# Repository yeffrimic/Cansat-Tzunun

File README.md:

# 🌎 Estación de Calidad del Aire – Proyecto CanSat Tzunun

Este repositorio contiene el código, documentación, archivos de diseño y recursos educativos para implementar una **estación de monitoreo ambiental**, así como su versión miniaturizada adaptada al formato **CanSat**. El proyecto fue desarrollado por estudiantes de la **Universidad Mesoamericana, sede Quetzaltenango**, como una herramienta de medición ambiental portátil, educativa y de bajo costo.

---

## 🚀 Guía de Instalación – Heltec WiFi LoRa 32 (V3) en Arduino IDE

### Paso 1: Instalar el Arduino IDE
Descarga e instala la versión más reciente desde: [https://www.arduino.cc/en/software](https://www.arduino.cc/en/software)

### Paso 2: Añadir URL del Gestor de Placas
1. Abre Arduino IDE.
2. Ve a **Archivo → Preferencias**.
3. En **"Gestor de URLs adicionales de tarjetas"**, añade: https://resource.heltec.cn/download/package_heltec_esp32_index.json
### Paso 3: Instalar el soporte para Heltec
1. Ve a **Herramientas → Placa → Gestor de tarjetas**.
2. Busca **Heltec ESP32** y haz clic en *Instalar*.

### Paso 4: Seleccionar la placa correcta
1. En **Herramientas → Placa**, selecciona:  
**Heltec WiFi LoRa 32 (V3)**.
2. Configura:
- Flash Frequency: 80 MHz  
- Upload Speed: 115200  
- Partition Scheme: Default 4MB with spiffs

### Paso 5: Instalar librerías necesarias
Desde el **Gestor de Librerías**, instala:
- `Wire.h`
- `Adafruit BMP085`
- `AHTxx`
- `LoRa.h`
- `SD.h`
- `U8g2`
- Y las indicadas en la carpeta `codigo/`

---

## 📌 Descripción del Proyecto

La estación mide:
- Temperatura y humedad
- Presión atmosférica
- Gases y partículas
- Aceleración y orientación (para CanSat)
- GPS (en versiones avanzadas)

### Versiones:
- **Estación Fija:** Para instalación permanente.
- **CanSat:** Miniatura para lanzamientos simulados.

Ambas versiones transmiten datos por **LoRa/WiFi** y se visualizan con **Node-RED**.

---

## 🧠 Estructura del Repositorio

├── codigo/ # Códigos para Heltec ESP32 Lora V3

├── modelos_3d/ # Archivos STL para impresión 3D

├── node-red/ # Flujos exportados de Node-RED

├── kicad/ # Archivos del diseño PCB en KiCad

### Contenido detallado

#### `codigo/`
- Lectura de sensores
- Comunicación LoRa/WiFi
- Escritura en SD
- Pantalla OLED

#### `modelos_3d/`
- Archivos STL para impresión FDM
- Versiones fija y CanSat

#### `node-red/`
- Dashboards
- Descarga de datos (CSV, JSON)
- Endpoints y APIs

#### `kicad/`
- Archivos `.kicad_pcb`, `.sch`, `.kicad_pro`
- Gerbers, BOM y diagramas

#### `videos/`
- Armado y soldadura
- Carga de código
- Uso de Node-RED
- Diagnóstico

---

## 🧩 Hardware Utilizado

Diseño PCB en **KiCad**, optimizado para **JLCPCB** con diámetro de 10 cm.

### Componentes:
- Heltec WiFi LoRa 32 V3 (ESP32)
- GPS
- MPU6050
- BMP180
- AHT10
- Módulo GSM
- Sensor de partículas
- Conectores de expansión
- Pantalla OLED

---

## 🌐 Plataforma Node-RED

- Visualización en tiempo real
- Descarga de históricos
- Redireccionamiento automático
- Endpoints personalizados

Instalable en Raspberry Pi, PC o nube.

---

## ✅ Requisitos

- Arduino IDE
- Librerías para sensores (ver `codigo/`)
- Node-RED
- KiCad 7.x
- Fuente 5V 1A
- microSD (<8 GB) para CanSat

---

## 📄 Licencia

Este proyecto está bajo la Licencia **MIT**.  
Puedes usarlo, modificarlo y compartirlo libremente con los créditos correspondientes.

---

## 👨‍🏫 Créditos

**Universidad Mesoamericana** – Facultad de Ingeniería  
**Proyecto CanSat Tzunun 2024** – Sede Quetzaltenango  
Docente responsable: *[Nombre del asesor]*

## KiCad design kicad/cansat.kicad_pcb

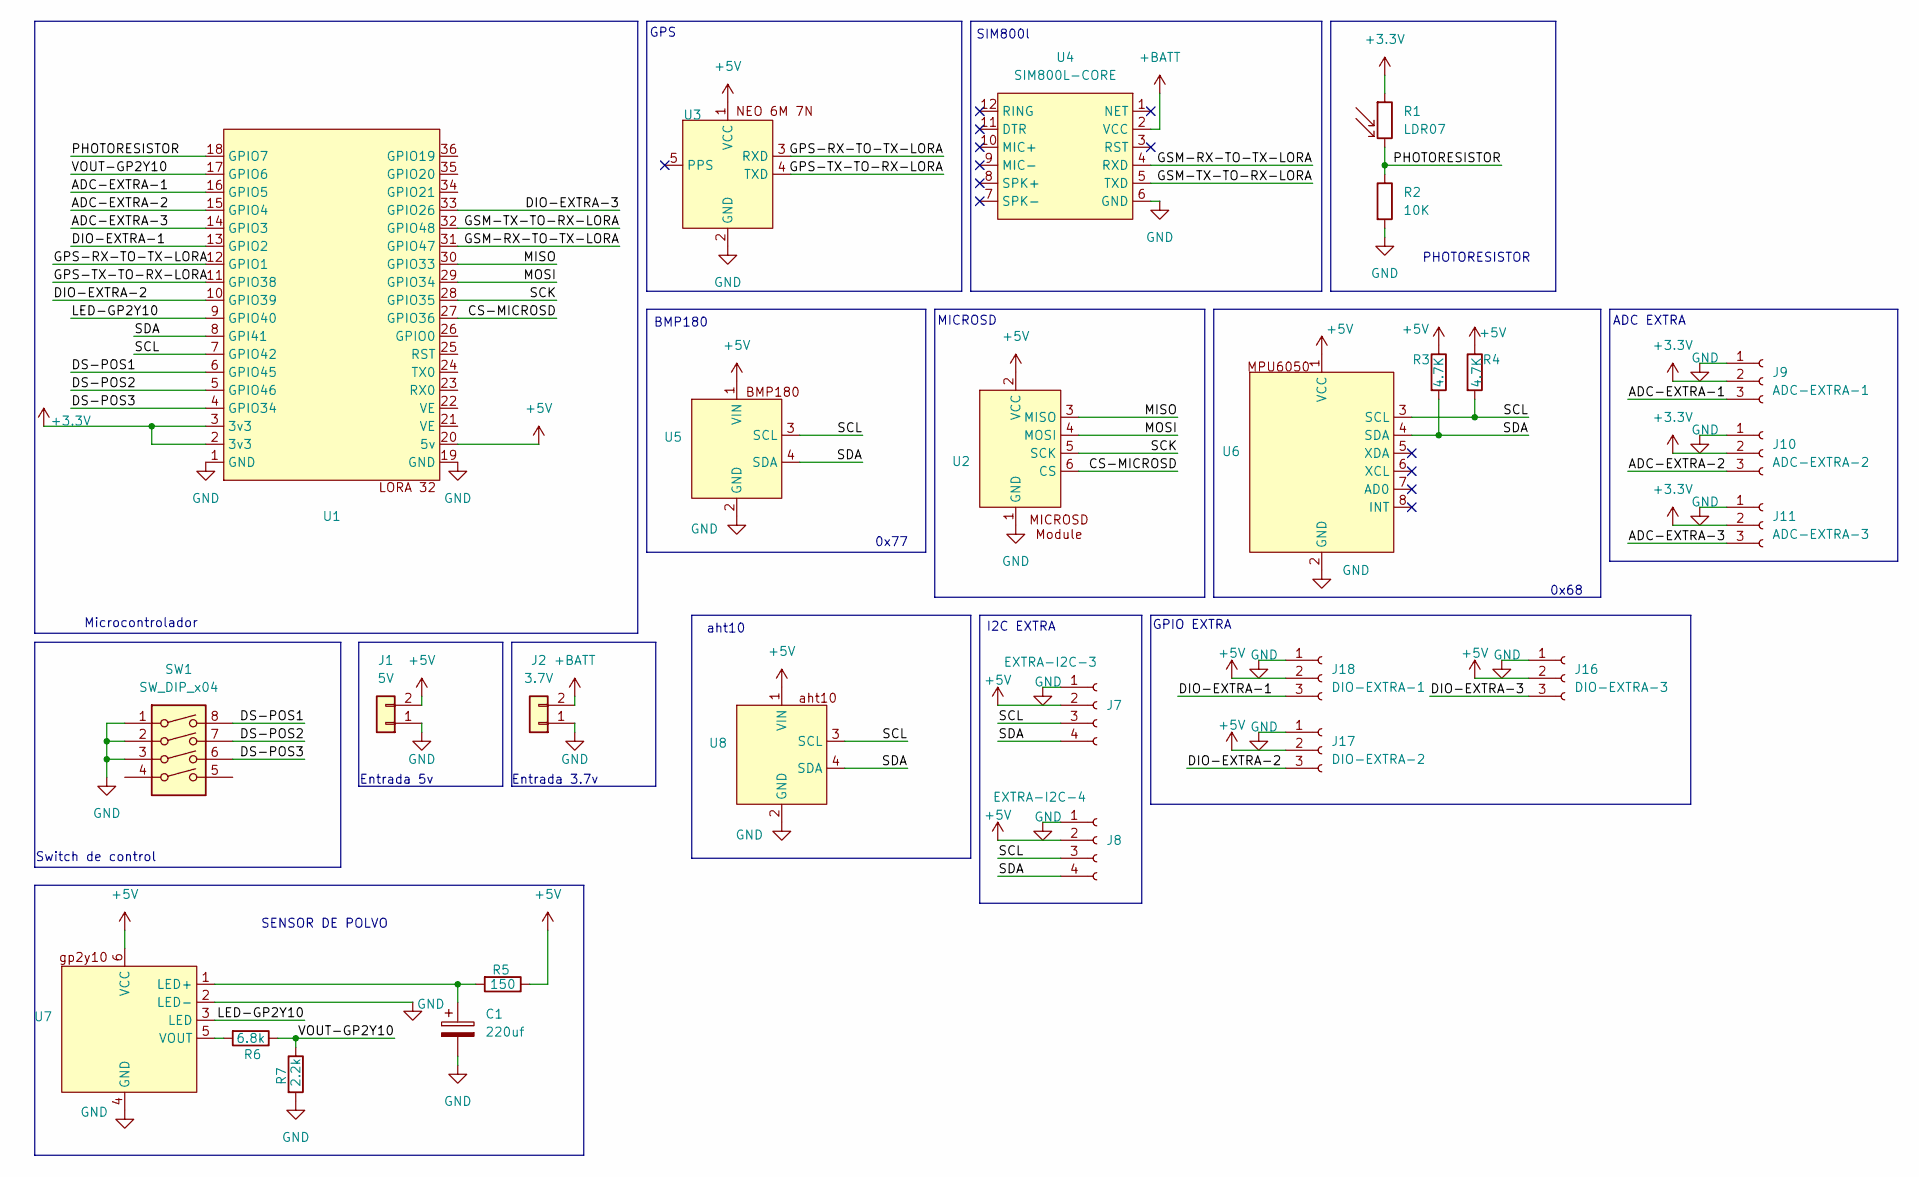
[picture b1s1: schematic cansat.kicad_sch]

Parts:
C1: 220uf; CP_Radial_D5.0mm_P2.50mm
J1: 5V; PinHeader_1x02_P2.54mm_Vertical
J2: 3.7V; PinHeader_1x02_P2.54mm_Vertical
J7: EXTRA-I2C-3; PinHeader_1x04_P2.54mm_Vertical
J8: EXTRA-I2C-4; PinHeader_1x04_P2.54mm_Vertical
J9: ADC-EXTRA-1; PinHeader_1x03_P2.54mm_Vertical
J10: ADC-EXTRA-2; PinHeader_1x03_P2.54mm_Vertical
J11: ADC-EXTRA-3; PinHeader_1x03_P2.54mm_Vertical
J16: DIO-EXTRA-3; PinHeader_1x03_P2.54mm_Vertical
J17: DIO-EXTRA-2; PinHeader_1x03_P2.54mm_Vertical
J18: DIO-EXTRA-1; PinHeader_1x03_P2.54mm_Vertical
R1: LDR07; R_LDR_5.1x4.3mm_P3.4mm_Vertical
R2: 10K; R_Axial_DIN0207_L6.3mm_D2.5mm_P10.16mm_Horizontal
R3, R4: 4.7K; R_Axial_DIN0207_L6.3mm_D2.5mm_P10.16mm_Horizontal
R5: 150; R_Axial_DIN0207_L6.3mm_D2.5mm_P10.16mm_Horizontal
R6: 6.8k; R_Axial_DIN0207_L6.3mm_D2.5mm_P10.16mm_Horizontal
R7: 2.2k; R_Axial_DIN0207_L6.3mm_D2.5mm_P10.16mm_Horizontal
SW1: SW_DIP_x04; SW_DIP_SPSTx04_Slide_9.78x12.34mm_W7.62mm_P2.54mm
U1: MODULE_WIFI_KIT_32__V3_
U2: micro sd
U3: neo6 gps module
U4: SIM800L-CORE
U5, U8: module_bmp180
U6: module_mpu6050
U7: PinHeader_1x06_P2.54mm_Vertical

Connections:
+3.3V: J9.2, J10.2, J11.2, R1.1, U1.2 (3v3), U1.3 (3v3)
+5V: J1.2, J7.2, J8.2, J16.2, J17.2, J18.2, R3.1, R4.1, R5.1, U1.20 (5v), U2.2 (VCC), U3.1 (VCC), U5.1 (VIN), U6.1 (VCC), U7.6 (VCC), U8.1 (VIN)
+BATT: J2.2, U4.2 (VCC)
/ADC-EXTRA-1: J9.3, U1.16 (GPIO5)
/ADC-EXTRA-2: J10.3, U1.15 (GPIO4)
/ADC-EXTRA-3: J11.3, U1.14 (GPIO3)
/CS-MICROSD: U1.27 (GPIO36), U2.6 (CS)
/DIO-EXTRA-1: J18.3, U1.13 (GPIO2)
/DIO-EXTRA-2: J17.3, U1.10 (GPIO39)
/DIO-EXTRA-3: J16.3, U1.33 (GPIO26)
/DS-POS1: SW1.8, U1.6 (GPIO45)
/DS-POS2: SW1.7, U1.5 (GPIO46)
/DS-POS3: SW1.6, U1.4 (GPIO34)
/GPS-RX-TO-TX-LORA: U1.12 (GPIO1), U3.3 (RXD)
/GPS-TX-TO-RX-LORA: U1.11 (GPIO38), U3.4 (TXD)
/GSM-RX-TO-TX-LORA: U1.31 (GPIO47), U4.4 (RXD)
/GSM-TX-TO-RX-LORA: U1.32 (GPIO48), U4.5 (TXD)
/LED-GP2Y10: U1.9 (GPIO40), U7.3 (LED)
/MISO: U1.30 (GPIO33), U2.3 (MISO)
/MOSI: U1.29 (GPIO34), U2.4 (MOSI)
/PHOTORESISTOR: R1.2, R2.1, U1.18 (GPIO7)
/SCK: U1.28 (GPIO35), U2.5 (SCK)
/SCL: J7.3, J8.3, R4.2, U1.7 (GPIO42), U5.3 (SCL), U6.3 (SCL), U8.3 (SCL)
/SDA: J7.4, J8.4, R3.2, U1.8 (GPI41), U5.4 (SDA), U6.4 (SDA), U8.4 (SDA)
/VOUT-GP2Y10: R6.1, R7.1, U1.17 (GPIO6)
GND: C1.2, J1.1, J2.1, J7.1, J8.1, J9.1, J10.1, J11.1, J16.1, J17.1, J18.1, R2.2, R7.2, SW1.1, SW1.2, SW1.3, U1.1 (GND), U1.19 (GND), U2.1 (GND), U3.2 (GND), U4.6 (GND), U5.2 (GND), U6.2 (GND), U7.2 (LED-), U7.4 (GND), U8.2 (GND)
unnamed: C1.1, R5.2, U7.1 (LED+)
unnamed: R6.2, U7.5 (VOUT)

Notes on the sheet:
SIM800l
ADC EXTRA
Switch de control
PHOTORESISTOR
aht10
SENSOR DE POLVO
0x77
BMP180
Entrada 5v
GPS
GPIO EXTRA
0x68
Entrada 3.7v
I2C EXTRA
Microcontrolador
MICROSD

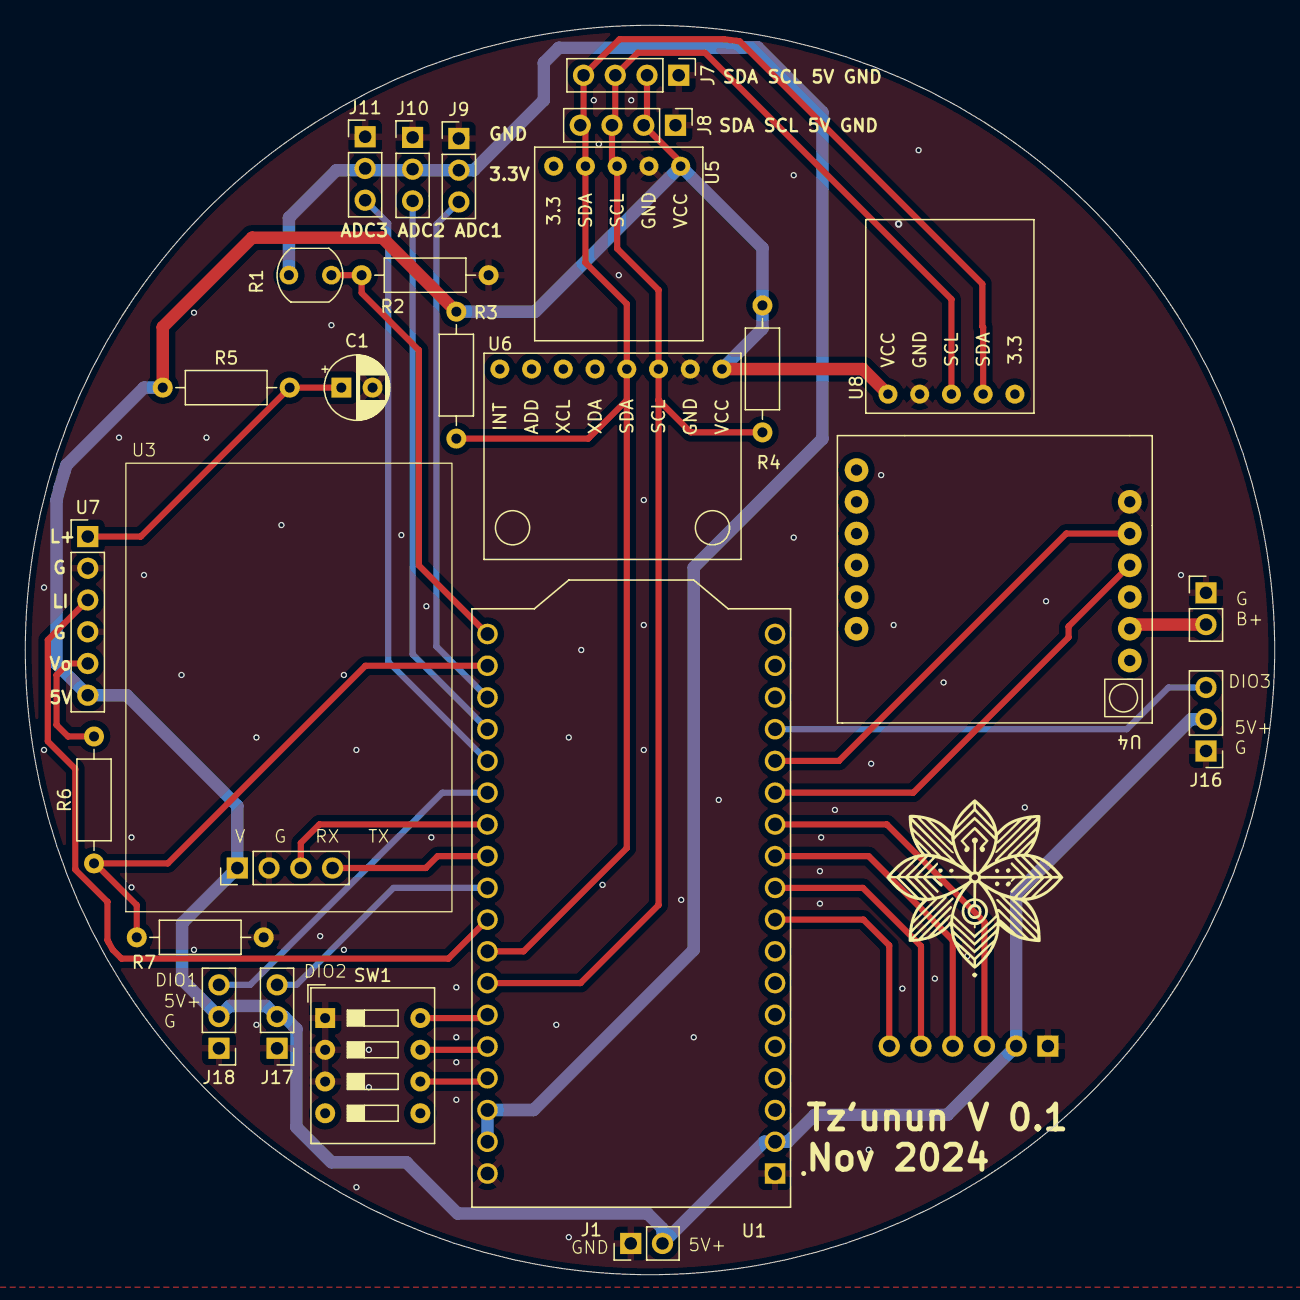
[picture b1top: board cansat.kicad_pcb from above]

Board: 4 copper layers, 100.0 x 100.0 mm, 27 parts (1 on the bottom side), 28 nets.

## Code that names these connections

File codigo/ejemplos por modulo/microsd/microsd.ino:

/*
 * Manejo de tarjeta MicroSD con SPI personalizado
 * Conexiones Heltec LoRa 32 V3:
 * - SCK  = GPIO35
 * - MISO = GPIO33
 * - MOSI = GPIO34
 * - CS   = GPIO36
 * 
 * Librería SD modificada para usar pines no estándar
 */

#include <SPI.h>
#include <SD.h>

// Configuración de pines SPI personalizados
const int SCK_PIN = 35;
const int MISO_PIN = 33;
const int MOSI_PIN = 34;
const int CS_PIN = 36;

// Objeto SPI personalizado
SPIClass customSPI(VSPI);

void setup() {
  Serial.begin(115200);
  while(!Serial); // Esperar conexión serial en placas con USB nativo

  Serial.println("\nProyecto Tzunun - Sistema de Archivos en MicroSD");
  
  // Configurar SPI con pines personalizados
  customSPI.begin(SCK_PIN, MISO_PIN, MOSI_PIN, CS_PIN);
  
  Serial.println("Inicializando tarjeta SD...");
  if(!SD.begin(CS_PIN, customSPI)) {
    Serial.println("¡Error al inicializar la tarjeta SD!");
    Serial.println("Verifica:");
    Serial.println("1. Conexiones de los pines");
    Serial.println("2. Formato de la tarjeta (FAT32)");
    Serial.println("3. Que la tarjeta esté insertada correctamente");
    return;
  }
  
  Serial.println("Tarjeta SD inicializada correctamente");
  
  // Crear archivo de prueba
  crearArchivo("/prueba.txt");
  
  // Leer archivo
  leerArchivo("/prueba.txt");
  
  // Listar directorio raíz
  listarDirectorio("/");
}

void loop() {
  // Nada en el loop para este ejemplo
}

// Función para crear/sobreescribir archivo
void crearArchivo(const char* filename) {
  File archivo = SD.open(filename, FILE_WRITE);
  
  if(archivo) {
    Serial.print("\nEscribiendo en archivo: ");
    Serial.println(filename);
    
    archivo.println("Datos de prueba - Proyecto Tzunun");
    archivo.println("Fecha: " + obtenerFecha());
    archivo.println("Hora: " + obtenerHora());
    archivo.println("Valor aleatorio: " + String(random(100)));
    
    archivo.close();
    Serial.println("Escritura completada");
  } else {
    Serial.print("Error al abrir ");
    Serial.println(filename);
  }
}

// Función para leer archivo
void leerArchivo(const char* filename) {
  File archivo = SD.open(filename);
  
  if(archivo) {
    Serial.print("\nLeyendo archivo: ");
    Serial.println(filename);
    
    while(archivo.available()) {
      Serial.write(archivo.read());
    }
    archivo.close();
  } else {
    Serial.print("Error al leer ");
    Serial.println(filename);
  }
}

// Función para listar directorios
void listarDirectorio(const char* dirname) {
  Serial.print("\nContenido del directorio: ");
  Serial.println(dirname);

  File root = SD.open(dirname);
  
  if(!root) {
    Serial.println("Error al abrir directorio");
    return;
  }
  
  if(!root.isDirectory()) {
    Serial.println("No es un directorio");
    return;
  }

  File entry = root.openNextFile();
  while(entry) {
    if(entry.isDirectory()) {
      Serial.print("DIR : ");
      Serial.println(entry.name());
    } else {
      Serial.print("FILE: ");
      Serial.print(entry.name());
      Serial.print("\tTAMAÑO: ");
      Serial.println(entry.size());
    }
    entry = root.openNextFile();
  }
  
  root.close();
}

// Función para obtener fecha ficticia (implementar RTC para precisión)
String obtenerFecha() {
  return "2023-11-15";
}

// Función para obtener hora ficticia
String obtenerHora() {
  return "14:30:00";
}

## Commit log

2025-05-14 Node-red nodes
2025-05-14 Rename flows.json to node-red/flows.json
2025-05-18 Rename Diseño_Cansat.3mf to 3d/Diseño_Cansat.3mf
2025-05-18 Rename Estacion_Meteorologica.3mf to 3d/Estacion_Meteorologica.3mf
